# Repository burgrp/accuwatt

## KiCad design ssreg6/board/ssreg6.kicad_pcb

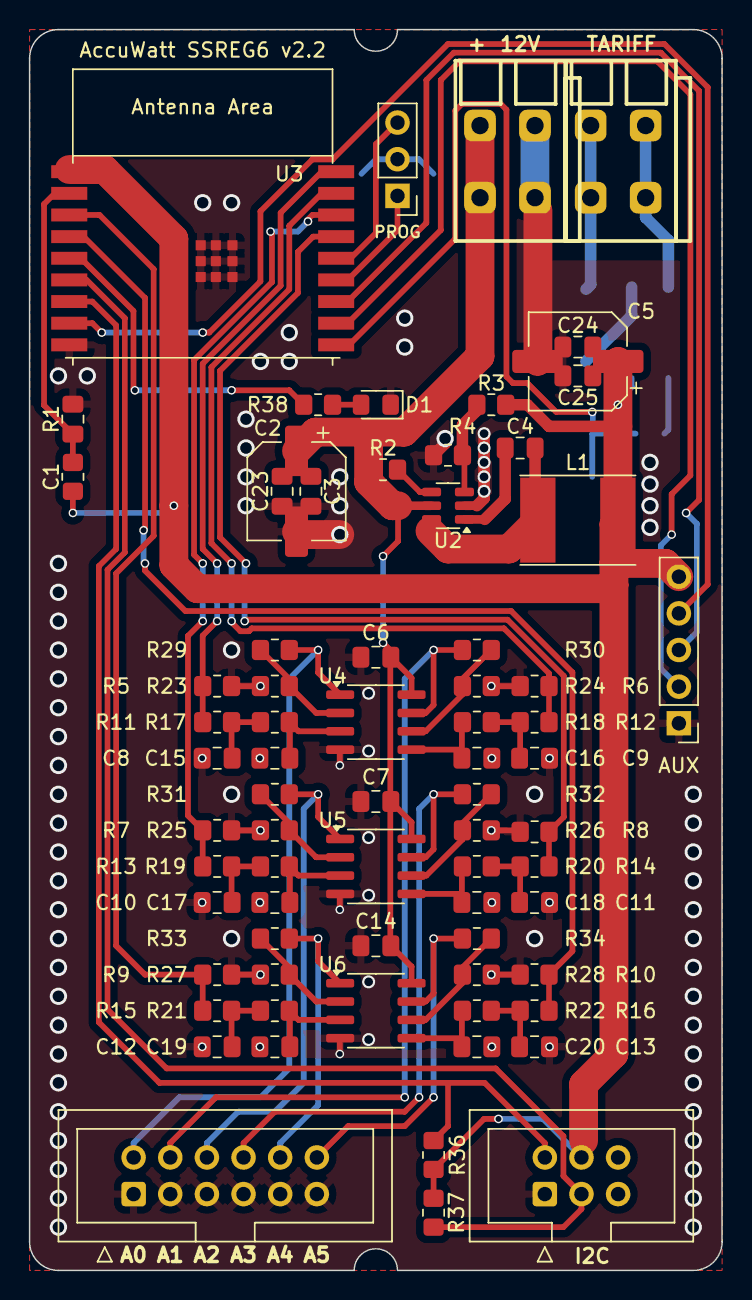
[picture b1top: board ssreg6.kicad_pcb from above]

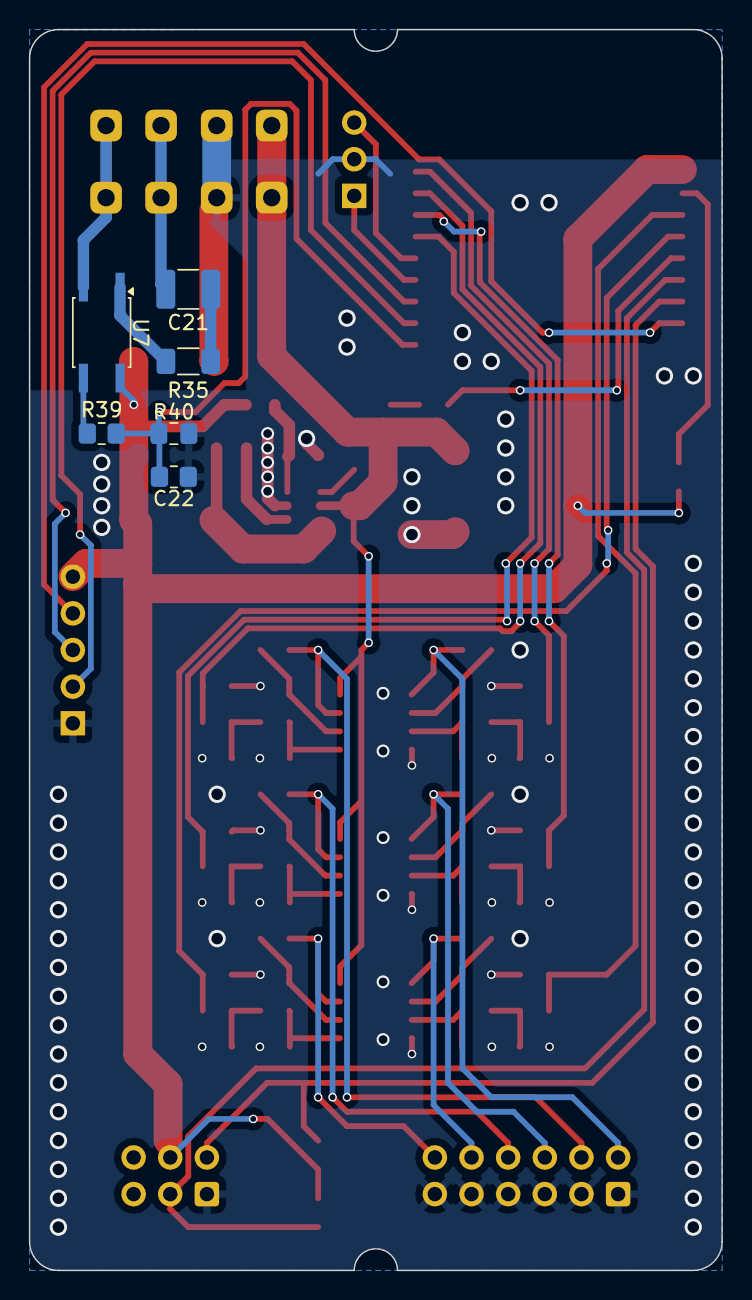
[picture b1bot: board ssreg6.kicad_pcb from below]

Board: 2 copper layers, 48.0 x 86.0 mm, 79 parts (6 on the bottom side), 53 nets.

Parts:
C1, C22: 1u; C_0805_2012Metric_Pad1.18x1.45mm_HandSolder
C2, C5: 100u/16V; CP_Elec_6.3x5.4
C3, C23, C24, C25: 10u/16V; C_0805_2012Metric_Pad1.18x1.45mm_HandSolder
C4, C6, C7, C8, C9, C10, C11, C12, C13, C14, C15, C16, C17, C18, C19, C20: 100n; C_0805_2012Metric_Pad1.18x1.45mm_HandSolder
C21: 100n; C_1210_3225Metric_Pad1.33x2.70mm_HandSolder
D1: LED; LED_0805_2012Metric_Pad1.15x1.40mm_HandSolder
DO1: Regulators; IDC-Header_2x06_P2.54mm_Vertical
I2C1: I2C; IDC-Header_2x03_P2.54mm_Vertical
J1: PROG; PinHeader_1x03_P2.54mm_Vertical
J2: AUX; PinHeader_1x05_P2.54mm_Vertical
L1: 6.8uH; CKCS6028
R1: 10k; R_0805_2012Metric_Pad1.20x1.40mm_HandSolder
R2, R5, R6, R7, R8, R9, R10, R23, R24, R25, R26, R27, R28: 100k; R_0805_2012Metric_Pad1.20x1.40mm_HandSolder
R3: 30k 1%; R_0805_2012Metric_Pad1.20x1.40mm_HandSolder
R4: 6.65k 1%; R_0805_2012Metric_Pad1.20x1.40mm_HandSolder
R11, R12, R13, R14, R15, R16, R17, R18, R19, R20, R21, R22, R36, R37, R39: 1k5; R_0805_2012Metric_Pad1.20x1.40mm_HandSolder
R29, R30, R31, R32, R33, R34, R40: 56k; R_0805_2012Metric_Pad1.20x1.40mm_HandSolder
R35: 1k5; R_1206_3216Metric_Pad1.30x1.75mm_HandSolder
R38: 270R; R_0805_2012Metric_Pad1.20x1.40mm_HandSolder
U2: FR8205; SOT-23-6
U3: ESP32-C3-WROOM-02; ESP32-C3-WROOM-02-Handsolder
U4, U5, U6: LM358; SOIC-8_3.9x4.9mm_P1.27mm
U7: LTV-354T; SO-4_4.4x3.6mm_P2.54mm
X1: 12V; DG235-3.81-02P
X2: TARIFF; DG235-3.81-02P

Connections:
+3V3: C5.1, C24.1, C25.1, I2C1.4 (3V3), J2.5, L1.2, R1.2, R3.2, R36.2, R37.1, U3.1 (3V3), U7.4
+12V: C2.1, C3.1, C6.1, C7.1, C14.1, C23.1, R2.2, U2.5 (VIN), U4.8 (V+), U5.8 (V+), U6.8 (V+), X1.2
/AOUT0: DO1.2, R29.2, U4.1
/AOUT1: DO1.4, R30.2, U4.7
/AOUT2: DO1.6, R31.2, U5.1
/AOUT3: DO1.8, R32.2, U5.7
/AOUT4: DO1.10, R33.2, U6.1
/AOUT5: DO1.12, R34.2, U6.7
/AUX0: J2.2, U3.11 (GPIO20/U0RXD)
/AUX1: J2.3, U3.12 (GPIO21/U0TXD)
/AUX2: J2.4, U3.8 (GPIO9)
/DOUT0: R5.2, R11.1, U3.18 (GPIO0/ADC1_CH0/XTAL_32K_P)
/DOUT1: R6.2, R12.1, U3.17 (GPIO1/ADC1_CH1/XTAL_32K_N)
/DOUT2: R7.2, R13.1, U3.16 (GPIO2/ADC1_CH2)
/DOUT3: R8.2, R14.1, U3.15 (GPIO3/ADC1_CH3)
/DOUT4: R9.2, R15.1, U3.3 (GPIO4/ADC1_CH4)
/DOUT5: R10.2, R16.1, U3.4 (GPIO5/ADC2_CH0)
/LED: R38.1, U3.5 (GPIO6)
/SCL: I2C1.2 (SCL), R36.1, U3.7 (GPIO8)
/SDA: I2C1.3 (SDA), R37.2, U3.6 (GPIO7)
/TARIFF: C22.2, R39.2, R40.1, U3.10 (GPIO10)
GND: C1.1, C2.2, C3.2, C5.2, C6.2, C7.2, C8.2, C9.2, C10.2, C11.2, C12.2, C13.2, C14.2, C15.2, C16.2, C17.2, C18.2, C19.2, C20.2, C22.1, C23.2, C24.2, C25.2, D1.1 (K), DO1.1, DO1.3, DO1.5, DO1.7, DO1.9, DO1.11, I2C1.1 (GND), J1.2, J2.1, R4.1, R5.1, R6.1, R7.1, R8.1, R9.1, R10.1, R23.2, R24.2, R25.2, R26.2, R27.2, R28.2, R40.2, U2.2 (GND), U3.9 (GND), U3.19 (GND), U4.4 (V-), U5.4 (V-), U6.4 (V-), X1.1
unnamed: C8.1, R11.2, R17.1
unnamed: C9.1, R12.2, R18.1
unnamed: C10.1, R13.2, R19.1
unnamed: C11.1, R14.2, R20.1
unnamed: C12.1, R15.2, R21.1
unnamed: C13.1, R16.2, R22.1
unnamed: C21.1, R35.2
unnamed: D1.2 (A), R38.2
unnamed: J1.1, U3.13 (GPIO18/USB_D-)
unnamed: J1.3, U3.14 (GPIO19/USB_D+)
unnamed: R35.1, U7.1
unnamed: R39.1, U7.3
unnamed: C4.1, U2.1 (BST)
unnamed: R3.1, R4.2, U2.3 (FB)
unnamed: C4.2, L1.1, U2.6 (LX)
unnamed: R2.1, U2.4 (SHDN)
unnamed: C1.2, R1.1, U3.2 (EN/CHIP_PU)
unnamed: C15.1, R17.2, U4.3 (+)
unnamed: R23.1, R29.1, U4.2 (-)
unnamed: C16.1, R18.2, U4.5 (+)
unnamed: R24.1, R30.1, U4.6 (-)
unnamed: C17.1, R19.2, U5.3 (+)
unnamed: R25.1, R31.1, U5.2 (-)
unnamed: C18.1, R20.2, U5.5 (+)
unnamed: R26.1, R32.1, U5.6 (-)
unnamed: C19.1, R21.2, U6.3 (+)
unnamed: R27.1, R33.1, U6.2 (-)
unnamed: C20.1, R22.2, U6.5 (+)
unnamed: R28.1, R34.1, U6.6 (-)
unnamed: U7.2, X2.1
unnamed: C21.2, X2.2

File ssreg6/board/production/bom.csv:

Designator,Footprint,Quantity,Value,LCSC Part #
"C1, C22",0805,2,1u,
"C10, C11, C12, C13, C14, C15, C16, C17, C18, C19, C20, C4, C6, C7, C8, C9",0805,16,100n,
"C2, C5",CP_Elec_6.3x5.4,2,100u/16V,
C21,1210,1,100n,
"C23, C24, C25, C3",0805,4,10u/16V,
D1,0805,1,LED,
DO1,IDC-Header_2x06_P2.54mm_Vertical,1,Regulators,
I2C1,IDC-Header_2x03_P2.54mm_Vertical,1,I2C,
J1,PinHeader_1x03_P2.54mm_Vertical,1,PROG,
J2,PinHeader_1x05_P2.54mm_Vertical,1,AUX,
L1,CKCS6028,1,6.8uH,
R1,0805,1,10k,
"R10, R2, R23, R24, R25, R26, R27, R28, R5, R6, R7, R8, R9",0805,13,100k,
"R11, R12, R13, R14, R15, R16, R17, R18, R19, R20, R21, R22, R36, R37, R39",0805,15,1k5,
"R29, R30, R31, R32, R33, R34, R40",0805,7,56k,
R3,0805,1,30k 1%,
R35,1206,1,1k5,
R38,0805,1,270R,
R4,0805,1,6.65k 1%,
U2,SOT-23-6,1,FR8205,
U3,ESP32-C3-WROOM-02-Handsolder,1,ESP32-C3-WROOM-02,
"U4, U5, U6",SOIC-8_3.9x4.9mm_P1.27mm,3,LM358,
U7,SO-4_4.4x3.6mm_P2.54mm,1,LTV-354T,
X1,DG235-3.81-02P,1,12V,
X2,DG235-3.81-02P,1,TARIFF,

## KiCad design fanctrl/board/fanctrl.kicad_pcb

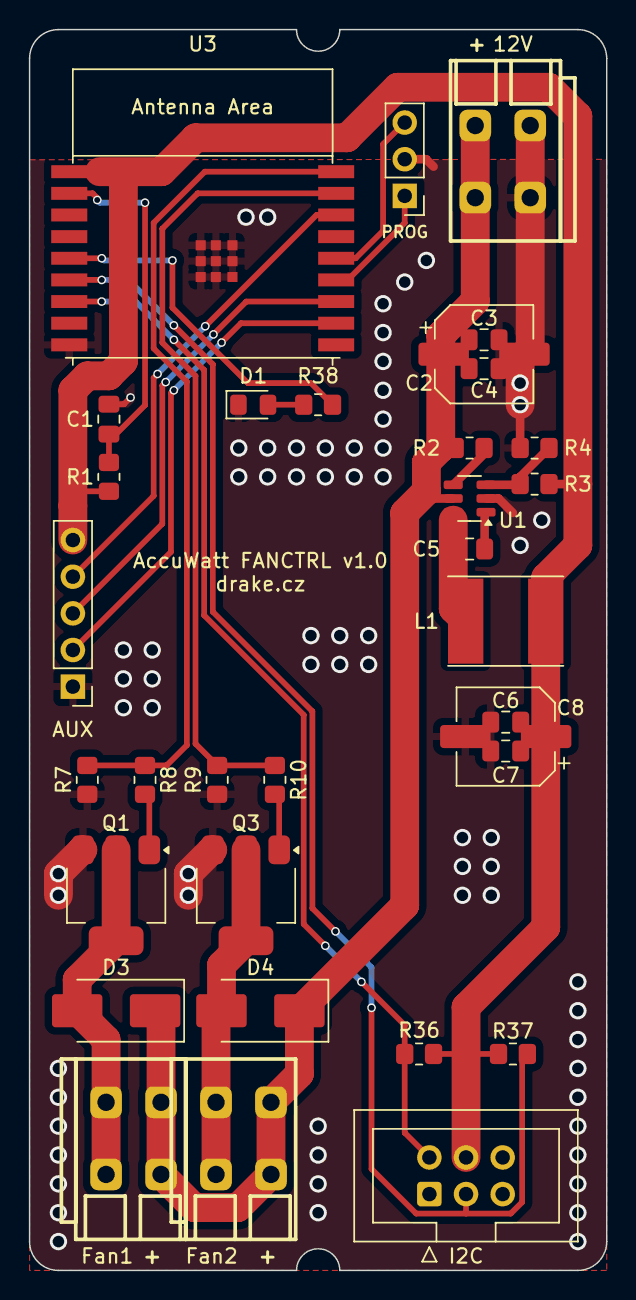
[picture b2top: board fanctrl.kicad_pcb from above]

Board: 2 copper layers, 40.0 x 86.0 mm, 33 parts (0 on the bottom side), 23 nets.

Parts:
C1: 1u; C_0805_2012Metric_Pad1.18x1.45mm_HandSolder
C2, C8: 100u/16V; CP_Elec_6.3x5.4
C3, C4, C6, C7: 10u/16V; C_0805_2012Metric_Pad1.18x1.45mm_HandSolder
C5: 100n; C_0805_2012Metric_Pad1.18x1.45mm_HandSolder
D1: LED; LED_0805_2012Metric_Pad1.15x1.40mm_HandSolder
D3, D4: SK22; D_SMB_Handsoldering
I2C1: I2C; IDC-Header_2x03_P2.54mm_Vertical
J1: PROG; PinHeader_1x03_P2.54mm_Vertical
J2: AUX; PinHeader_1x05_P2.54mm_Vertical
J3: Fan2; DG235-3.81-02P
J5: Fan1; DG235-3.81-02P
L1: 6.8uH; CKCS6028
Q1, Q3: YJM04N10A; SOT-223
R1, R7, R9: 10k; R_0805_2012Metric_Pad1.20x1.40mm_HandSolder
R2: 100k; R_0805_2012Metric_Pad1.20x1.40mm_HandSolder
R3: 30k 1%; R_0805_2012Metric_Pad1.20x1.40mm_HandSolder
R4: 6.65k 1%; R_0805_2012Metric_Pad1.20x1.40mm_HandSolder
R8, R10: 100; R_0805_2012Metric_Pad1.20x1.40mm_HandSolder
R36, R37: 1k5; R_0805_2012Metric_Pad1.20x1.40mm_HandSolder
R38: 270R; R_0805_2012Metric_Pad1.20x1.40mm_HandSolder
U1: FR8205; SOT-23-6
U3: ESP32-C3-WROOM-02; ESP32-C3-WROOM-02-Handsolder
X1: 12V; DG235-3.81-02P

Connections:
+3V3: C6.1, C7.1, C8.1, I2C1.4 (3V3), J2.5, L1.2, R1.2, R3.2, R36.2, R37.1, U3.1 (3V3)
+12V: C2.1, C3.1, C4.1, D3.1 (K), D4.1 (K), J3.2, J5.2, R2.2, U1.5 (VIN), X1.2
/AUX0: J2.2, U3.11 (GPIO20/U0RXD)
/AUX1: J2.3, U3.12 (GPIO21/U0TXD)
/AUX2: J2.4, U3.16 (GPIO2/ADC1_CH2)
/Driver1/SW_GND: D4.2 (A), J3.1, Q3.2 (D), Q3.4 (D)
/Driver/SW_GND: D3.2 (A), J5.1, Q1.2 (D), Q1.4 (D)
/FAN_1: R7.2, R8.1, U3.18 (GPIO0/ADC1_CH0/XTAL_32K_P)
/FAN_2: R9.2, R10.1, U3.17 (GPIO1/ADC1_CH1/XTAL_32K_N)
/LED: R38.1, U3.5 (GPIO6)
/SCL: I2C1.2 (SCL), R36.1, U3.7 (GPIO8)
/SDA: I2C1.3 (SDA), R37.2, U3.6 (GPIO7)
GND: C1.1, C2.2, C3.2, C4.2, C6.2, C7.2, C8.2, D1.1 (K), I2C1.1 (GND), J1.2, J2.1, Q1.3 (S), Q3.3 (S), R4.1, R7.1, R9.1, U1.2 (GND), U3.9 (GND), U3.19 (GND), X1.1
unnamed: D1.2 (A), R38.2
unnamed: J1.1, U3.13 (GPIO18/USB_D-)
unnamed: J1.3, U3.14 (GPIO19/USB_D+)
unnamed: Q1.1 (G), R8.2
unnamed: Q3.1 (G), R10.2
unnamed: C5.1, U1.1 (BST)
unnamed: R3.1, R4.2, U1.3 (FB)
unnamed: C5.2, L1.1, U1.6 (LX)
unnamed: R2.1, U1.4 (SHDN)
unnamed: C1.2, R1.1, U3.2 (EN/CHIP_PU)

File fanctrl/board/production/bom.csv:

Designator,Footprint,Quantity,Value,LCSC Part #
C1,0805,1,1u,
"C2, C8",CP_Elec_6.3x5.4,2,100u/16V,
"C3, C4, C6, C7",0805,4,10u/16V,
C5,0805,1,100n,
D1,0805,1,LED,
"D3, D4",D_SMB_Handsoldering,2,SK22,
I2C1,IDC-Header_2x03_P2.54mm_Vertical,1,I2C,
J1,PinHeader_1x03_P2.54mm_Vertical,1,PROG,
J2,PinHeader_1x05_P2.54mm_Vertical,1,AUX,
J3,DG235-3.81-02P,1,Fan2,
J5,DG235-3.81-02P,1,Fan1,
L1,CKCS6028,1,6.8uH,
"Q1, Q3",SOT-223,2,YJM04N10A,
"R1, R7, R9",0805,3,10k,
"R10, R8",0805,2,100,
R2,0805,1,100k,
R3,0805,1,30k 1%,
"R36, R37",0805,2,1k5,
R38,0805,1,270R,
R4,0805,1,6.65k 1%,
U1,SOT-23-6,1,FR8205,
U3,ESP32-C3-WROOM-02-Handsolder,1,ESP32-C3-WROOM-02,
X1,DG235-3.81-02P,1,12V,

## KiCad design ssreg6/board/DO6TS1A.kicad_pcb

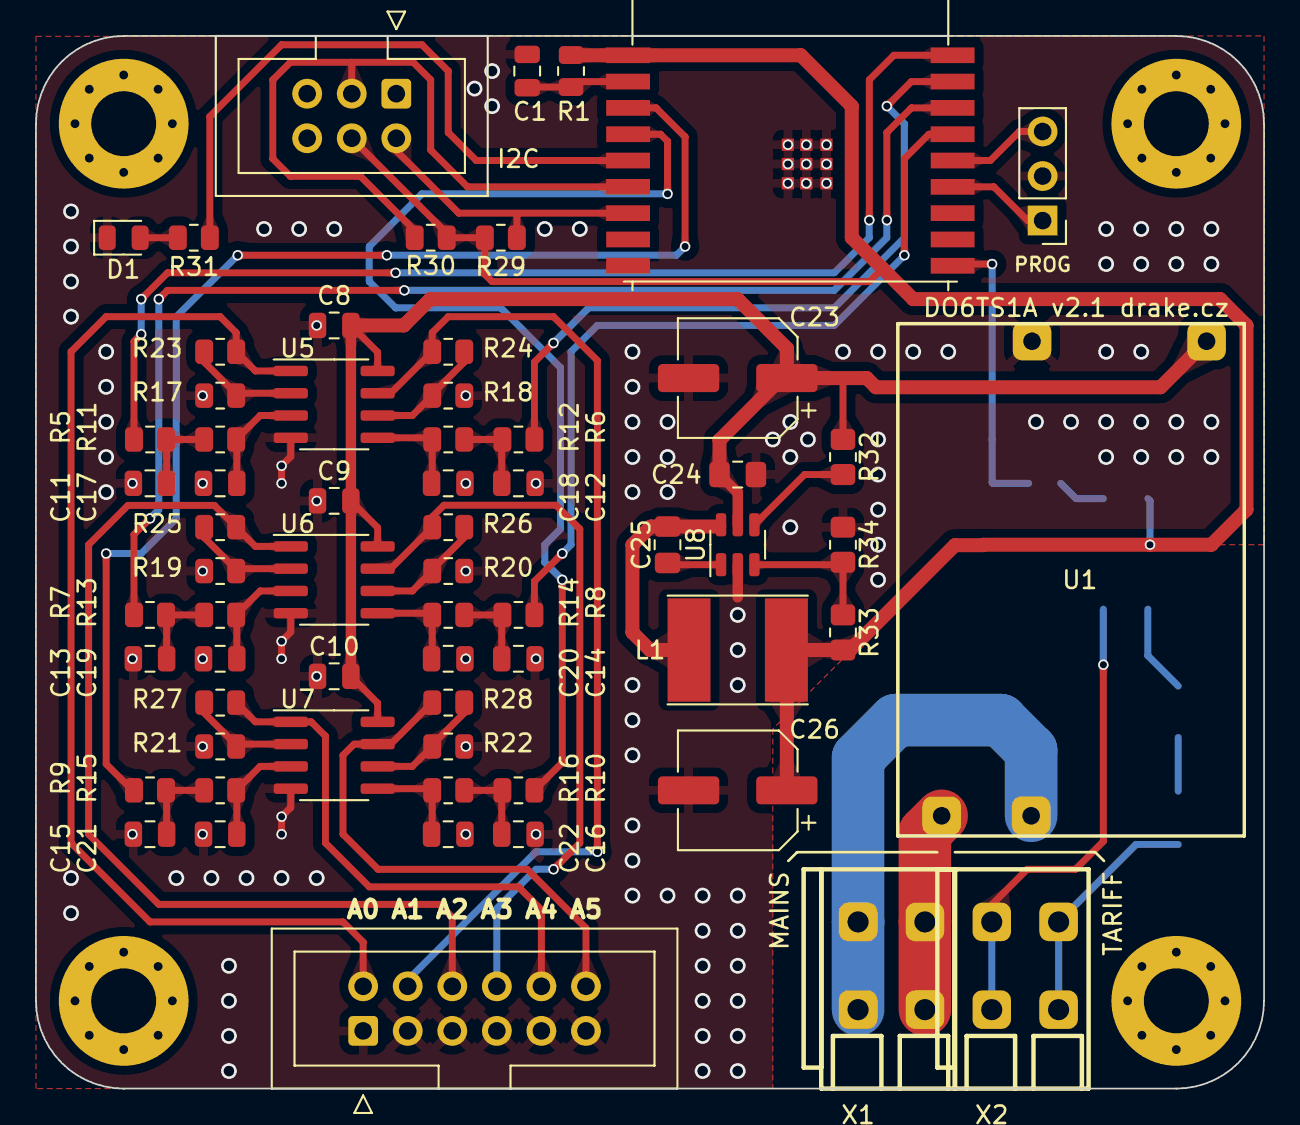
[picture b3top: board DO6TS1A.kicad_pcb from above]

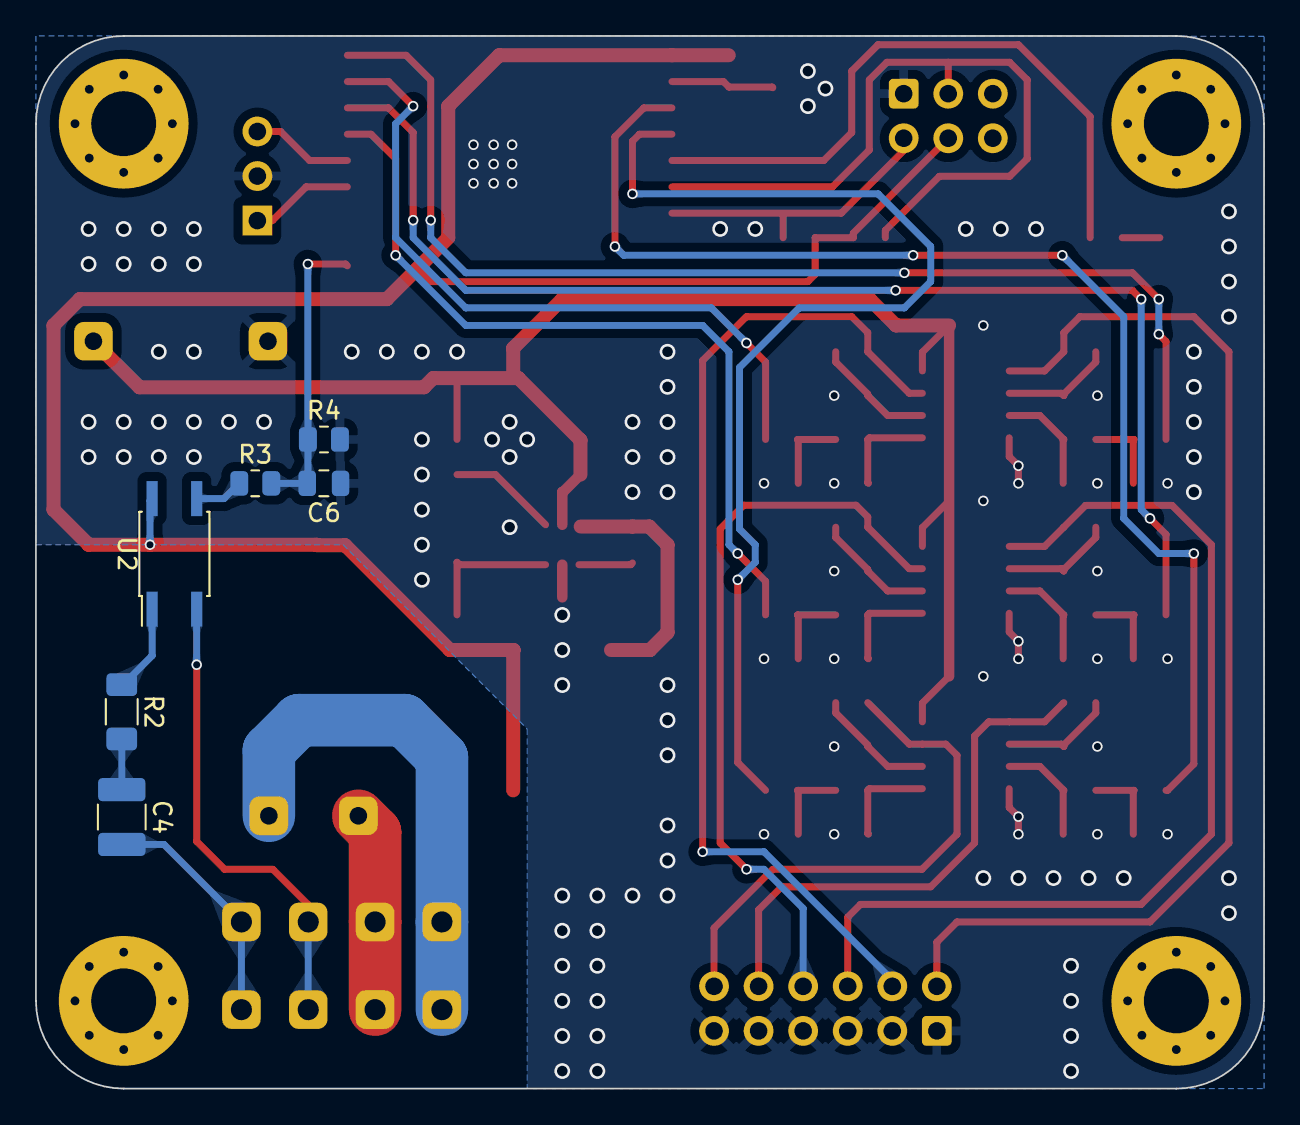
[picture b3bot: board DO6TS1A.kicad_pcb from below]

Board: 2 copper layers, 70.0 x 60.0 mm, 74 parts (6 on the bottom side), 52 nets.

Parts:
C1, C6: 1u; C_0805_2012Metric
C4: 100n; C_1210_3225Metric_Pad1.33x2.70mm_HandSolder
C8, C9, C10, C11, C12, C13, C14, C15, C16, C17, C18, C19, C20, C21, C22: 100n; C_0805_2012Metric
C23: 100u/16V; CP_Elec_6.3x5.4
C24, C25: 100n; C_0805_2012Metric_Pad1.18x1.45mm_HandSolder
C26: 100u/12V; CP_Elec_6.3x5.4
D1: LED; LED_0805_2012Metric
DO1: Regulators; IDC-Header_2x06_P2.54mm_Vertical
H1, H2, H3, H4: MountingHole; MountingHole_3.7mm_Pad_Via
I2C1: I2C; IDC-Header_2x03_P2.54mm_Vertical
J1: PROG; PinHeader_1x03_P2.54mm_Vertical
L1: 6.8uH; CKCS6028
R1: 10k; R_0805_2012Metric
R2: 1k5; R_1206_3216Metric_Pad1.30x1.75mm_HandSolder
R3, R5, R6, R7, R8, R9, R10, R11, R12, R13, R14, R15, R16, R29, R30: 1k5; R_0805_2012Metric
R4, R23, R24, R25, R26, R27, R28: 56k; R_0805_2012Metric
R17, R18, R19, R20, R21, R22: 100k; R_0805_2012Metric
R31: 270R; R_0805_2012Metric
R32: 100k; R_0805_2012Metric_Pad1.20x1.40mm_HandSolder
R33: 30k 1%; R_0805_2012Metric_Pad1.20x1.40mm_HandSolder
R34: 6.65k 1%; R_0805_2012Metric_Pad1.20x1.40mm_HandSolder
U1: YS-12V450A
U2: LTV-354T; SO-4_4.4x3.6mm_P2.54mm
U3: ESP32-C3-WROOM-02; ESP32-C3-WROOM-02 Handsolder
U5, U6, U7: LM358; SOIC-8_3.9x4.9mm_P1.27mm
U8: FR8205; SOT-23-6
X1: MAINS; DG235-3.81-02P
X2: TARIFF; DG235-3.81-02P

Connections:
+3V3: C26.1, I2C1.4 (3V3), L1.2, R1.2, R29.2, R30.1, R33.2, U2.4, U3.1 (3V3)
+12V: C8.1, C9.1, C10.1, C23.1, C24.2, R32.2, U1.4 (OUT+), U5.8 (V+), U6.8 (V+), U7.8 (V+), U8.5 (VIN)
/AOUT0: DO1.2, R23.2, U5.1
/AOUT1: DO1.4, R24.2, U5.7
/AOUT2: DO1.6, R25.2, U6.1
/AOUT3: DO1.8, R26.2, U6.7
/AOUT4: DO1.10, R27.2, U7.1
/AOUT5: DO1.12, R28.2, U7.7
/DOUT0: R5.1, U3.18 (GPIO0/ADC1_CH0/XTAL_32K_P)
/DOUT1: R6.1, U3.17 (GPIO1/ADC1_CH1/XTAL_32K_N)
/DOUT2: R7.1, U3.16 (GPIO2/ADC1_CH2)
/DOUT3: R8.1, U3.15 (GPIO3/ADC1_CH3)
/DOUT4: R9.1, U3.3 (GPIO4/ADC1_CH4)
/DOUT5: R10.1, U3.4 (GPIO5/ADC2_CH0)
/LED: R31.1, U3.5 (GPIO6)
/SCL: I2C1.2 (SCL), R29.1, U3.7 (GPIO8)
/SDA: I2C1.3 (SDA), R30.2, U3.6 (GPIO7)
/TARIFF: C6.2, R3.2, R4.1, U3.10 (GPIO10)
GND: C1.1, C6.1, C8.2, C9.2, C10.2, C11.2, C12.2, C13.2, C14.2, C15.2, C16.2, C17.2, C18.2, C19.2, C20.2, C21.2, C22.2, C23.2, C24.1, C26.2, D1.1 (K), DO1.1, DO1.3, DO1.5, DO1.7, DO1.9, DO1.11, I2C1.1 (GND), J1.2, R4.2, R17.2, R18.2, R19.2, R20.2, R21.2, R22.2, R34.1, U1.3 (OUT-), U3.9 (GND), U3.19 (GND), U5.4 (V-), U6.4 (V-), U7.4 (V-), U8.2 (GND)
unnamed: C4.1, R2.2
unnamed: C11.1, R5.2, R11.1
unnamed: C12.1, R6.2, R12.1
unnamed: C13.1, R7.2, R13.1
unnamed: C14.1, R8.2, R14.1
unnamed: C15.1, R9.2, R15.1
unnamed: C16.1, R10.2, R16.1
unnamed: D1.2 (A), R31.2
unnamed: J1.1, U3.13 (GPIO18/USB_D-)
unnamed: J1.3, U3.14 (GPIO19/USB_D+)
unnamed: R2.1, U2.1
unnamed: R3.1, U2.3
unnamed: U1.1 (LINE1), X1.1
unnamed: U1.2 (LINE2), X1.2
unnamed: C1.2, R1.1, U3.2 (EN/CHIP_PU)
unnamed: C17.1, R11.2, U5.3 (+)
unnamed: R17.1, R23.1, U5.2 (-)
unnamed: C18.1, R12.2, U5.5 (+)
unnamed: R18.1, R24.1, U5.6 (-)
unnamed: C19.1, R13.2, U6.3 (+)
unnamed: R19.1, R25.1, U6.2 (-)
unnamed: C20.1, R14.2, U6.5 (+)
unnamed: R20.1, R26.1, U6.6 (-)
unnamed: C21.1, R15.2, U7.3 (+)
unnamed: R21.1, R27.1, U7.2 (-)
unnamed: C22.1, R16.2, U7.5 (+)
unnamed: R22.1, R28.1, U7.6 (-)
unnamed: C25.1, U8.1 (BST)
unnamed: R33.1, R34.2, U8.3 (FB)
unnamed: C25.2, L1.1, U8.6 (LX)
unnamed: R32.1, U8.4 (SHDN)
unnamed: U2.2, X2.1
unnamed: C4.2, X2.2

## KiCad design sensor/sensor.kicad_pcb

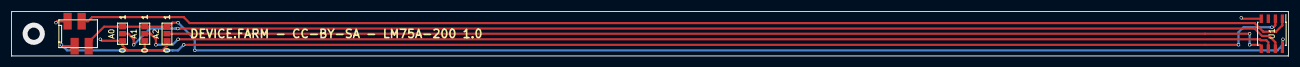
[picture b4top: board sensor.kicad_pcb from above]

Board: 2 copper layers, 230.0 x 8.0 mm, 5 parts (0 on the bottom side), 7 nets.

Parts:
A0, A1, A2: GS3
U1: LM75A; SOIC-8_3.9x4.9mm_Pitch1.27mm
X1: I2C; Micro-Match-FOB-4

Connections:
/SCL: U1.2, X1.2
/SDA: U1.1, X1.3
GND: A0.1, A1.1, A2.1, U1.4, X1.1
unnamed: A0.2, U1.7
unnamed: A1.2, U1.6
unnamed: A2.2, U1.5
VCC: A0.3, A1.3, A2.3, U1.8, X1.4

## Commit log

2023-06-26 call version
2024-10-26 library update
2024-10-26 fanctrl schema
2024-11-18 board WIP
2024-11-27 board design
2024-12-13 ceramic capacitors on PSU & JLC order
2026-06-17 Add package lockfile

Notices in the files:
sensor/sensor.kicad_pcb:
DEVICE.FARM - CC-BY-SA - LM75A-200 1.0
